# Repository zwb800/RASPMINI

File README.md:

# RASPMINI
Ardupilot Flight Controller HAT for raspberry pi

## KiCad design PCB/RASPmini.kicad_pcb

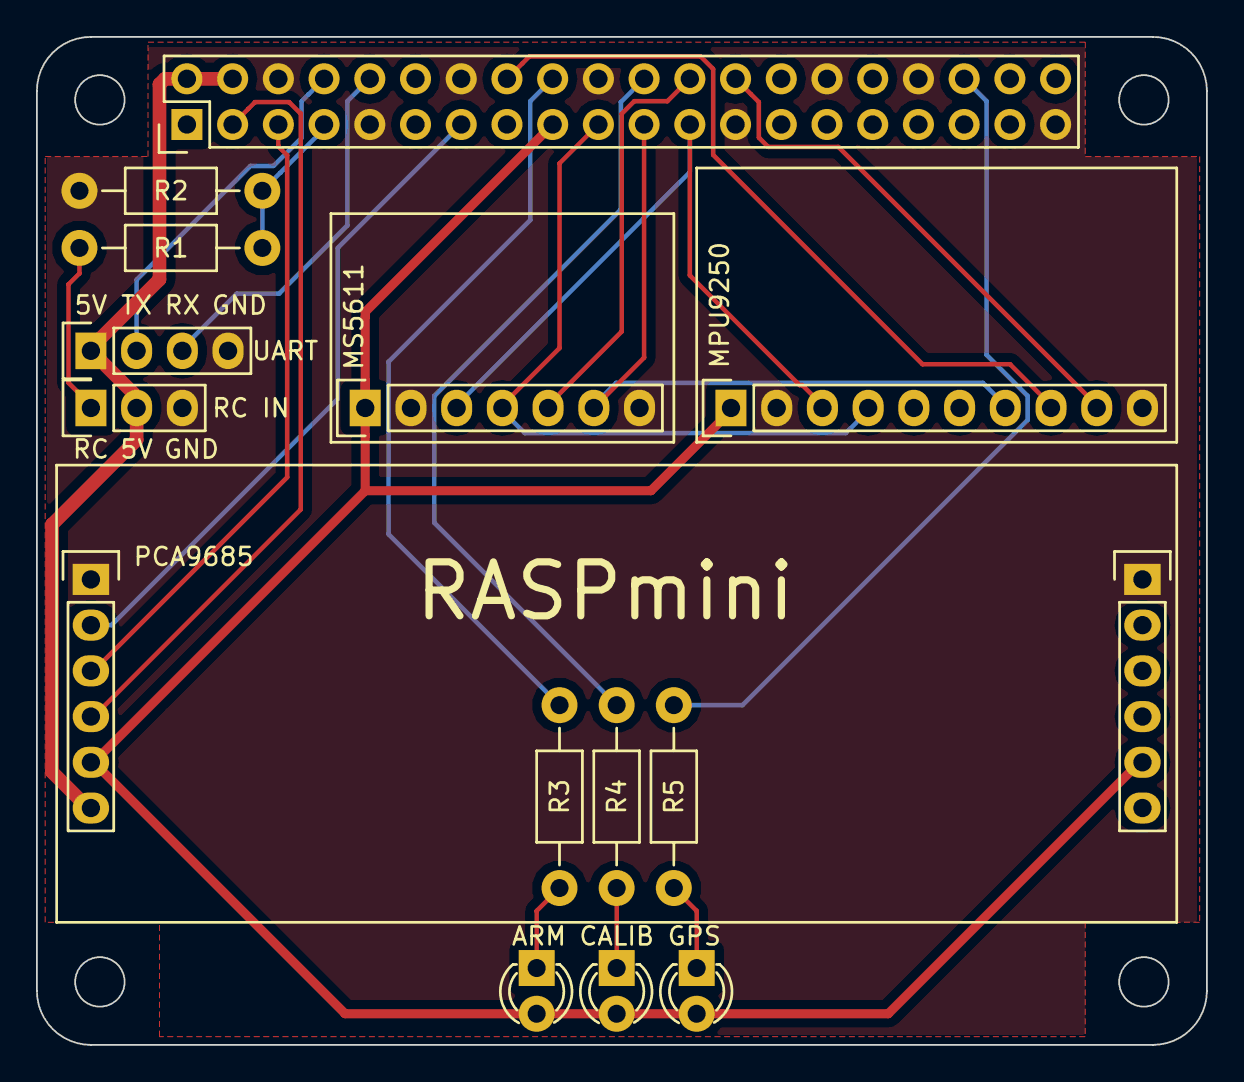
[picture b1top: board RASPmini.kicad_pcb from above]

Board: 2 copper layers, 65.0 x 56.0 mm, 14 parts (0 on the bottom side), 22 nets.

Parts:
D1: ARM; LED-3MM
D2: CALIB; LED-3MM
D3: GPS; LED-3MM
P0: Raspberry PI GPIO; Pin_Header_Straight_2x20
P1: MPU9250
P2: MS5611
P3: PCA9685
P5: UART; Pin_Header_Straight_1x04
P6: RC IN; Pin_Header_Straight_1x03
R1: 18K; Resistor_Horizontal_RM10mm
R2: 33K; Resistor_Horizontal_RM10mm
R3, R4, R5: 220; Resistor_Horizontal_RM10mm

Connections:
+3V3: D1.2, D2.2, D3.2, P0.1, P0.17, P1.1, P2.1, P3.5
+5V: P0.2, P0.4, P3.6, P5.1, P6.2
/CS_BARO: P0.24, P2.5
/CS_MPU: P0.26, P1.9
/EN_PWM: P0.13, P3.2
/LED_ARM: P0.18, R3.2
/LED_CALIBRATION: P0.22, R4.2
/LED_GPS: P0.36, R5.2
/MISO: P0.21, P1.7, P2.6
/MOSI: P0.19, P1.4, P2.4
/MPU_DRDY: P0.16, P1.8
/RC_INPUT: P0.7, R1.2, R2.1
/RXD: P0.10, P5.3
/SCL: P0.5, P3.3
/SCLK: P0.23, P1.3, P2.3
/SDA: P0.3, P3.4
/TXD: P0.8, P5.2
GND: P0.6, P0.9, P0.14, P0.20, P0.25, P0.30, P0.34, P0.39, P1.2, P1.10, P2.2, P2.7, P3.1, P5.4, P6.3, R2.2
unnamed: D1.1, R3.1
unnamed: D2.1, R4.1
unnamed: D3.1, R5.1
unnamed: P6.1, R1.1

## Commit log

2016-10-13 第一次打样
2016-10-13 添加OSHWA logo
2016-10-20 串口电源改为3.3v
2016-10-25 正式PCB
2019-04-27 fix: silk layer
